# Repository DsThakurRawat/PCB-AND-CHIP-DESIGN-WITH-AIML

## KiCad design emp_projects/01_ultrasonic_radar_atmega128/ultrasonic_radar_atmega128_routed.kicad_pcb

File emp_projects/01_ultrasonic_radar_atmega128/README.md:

# Ultrasonic Radar Model Using ATmega128

## 📌 Project Overview
**Course Experiment:** Electronic Measurement Practices (EMP)  
**PCB Architecture:** 2-Layer Controlled Design  
**Primary Controller:** ATmega128A  
**Deliverables Status:** Complete Manufacturing Package Verified (Gerbers, Drill, Pos CSV, iBOM, 3D Render)

---

## 🎯 Description & Operational Principles
Panoramic ultrasonic radar mapping station with ATmega128 MCU, SG90 servo sweep platform, HC-SR04 sonar module, 16x2 HD44780 LCD readout, and RS232 host telemetry.

### Key Features & Subsystems
- **Processor & Logic Core:** High-efficiency architecture designed for reliable embedded operation.
- **Power Management & Regulation:** Low-noise power rail distribution with dedicated filtering and bulk decouple stages.
- **Sensory & Peripheral Interfacing:** Industrial standard interconnect headers with ESD and reverse polarity protection.
- **Fabrication & Assembly Optimization:** Standard 0805 SMD passives and leaded THT power devices for high manufacturing yield and inspectability.

---

## 🛠️ Bill of Materials (BOM Summary)

| Reference | Component Value | Package / Footprint | Description |
|:---:|:---:|:---:|:---|
| `U1` | **ATmega128A** | `Package_QFP:TQFP-64_14x14mm_P0.8mm` | Circuit element |
| `U2` | **MAX232** | `Package_SO:SOIC-16_3.9x9.9mm_P1.27mm` | Circuit element |
| `U3` | **LM7805** | `Package_TO_SOT_SMD:TO-252-2` | Circuit element |
| `J1` | **HC_SR04_HDR** | `Connector_PinHeader_2.54mm:PinHeader_1x04_P2.54mm_Vertical` | Circuit element |
| `J2` | **SERVO_SG90** | `Connector_PinHeader_2.54mm:PinHeader_1x03_P2.54mm_Vertical` | Circuit element |
| `J3` | **LCD_16x2_HDR** | `Connector_PinHeader_2.54mm:PinHeader_1x16_P2.54mm_Vertical` | Circuit element |
| `J4` | **AVR_ISP_6PIN** | `Connector_PinHeader_2.54mm:PinHeader_2x03_P2.54mm_Vertical` | Circuit element |
| `J5` | **PWR_JACK** | `Connector_BarrelJack:BarrelJack_Horizontal` | Circuit element |
| `Y1` | **16MHz_XTAL** | `Crystal:Crystal_SMD_3225-4Pin_3.2x2.5mm` | Circuit element |
| `C1` | **100uF_16V** | `Capacitor_THT:CP_Radial_D6.3mm_P2.50mm` | Circuit element |
| `C2` | **100nF** | `Capacitor_SMD:C_0805_2012Metric` | Circuit element |
| `R1` | **10k_RST** | `Resistor_SMD:R_0805_2012Metric` | Circuit element |
| `SW1` | **RESET** | `Button_Switch_SMD:SW_Push_SPST_NO_Alps_SKRK` | Circuit element |
| `D1` | **PWR_LED** | `LED_SMD:LED_0805_2012Metric` | Circuit element |

---

## 🏭 Manufacturing Deliverables & Artifacts

All production files have been generated in `manufacturing/`:
- **Gerber Layers (RS-274X):** Copper, solder masks, silkscreen, and board edge cuts (`manufacturing/gerbers/`)
- **Excellon Drill Files:** Plated and non-plated drill hole coordinates (`manufacturing/gerbers/*.drl`)
- **Fabricator ZIP Archive:** Single upload archive for PCB fabrication houses (`manufacturing/ultrasonic_radar_atmega128_gerbers.zip`)
- **Pick-and-Place Position CSV:** Centroid data for automated SMT placement machines (`manufacturing/ultrasonic_radar_atmega128_pos.csv`)
- **Interactive HTML BOM:** High-efficiency browser inspection and interactive assembly tool (`manufacturing/ibom.html`)
- **Altium-Style 3D Render:** Photorealistic perspective view with floor reflection shaders (`manufacturing/ultrasonic_radar_atmega128_3d.png`)

---

## 📐 Mechanical & Layout Constraints
- **Board Outline:** 100.0 mm × 75.0 mm
- **Layer Count:** 2 Layers (FR-4, 1.6mm thickness, 1oz/2oz copper)
- **Minimum Trace Width:** 0.20 mm (8 mil)
- **Minimum Clearance:** 0.20 mm (8 mil)
- **Via Drill / Diameter:** 0.40 mm drill / 0.80 mm annular ring pad

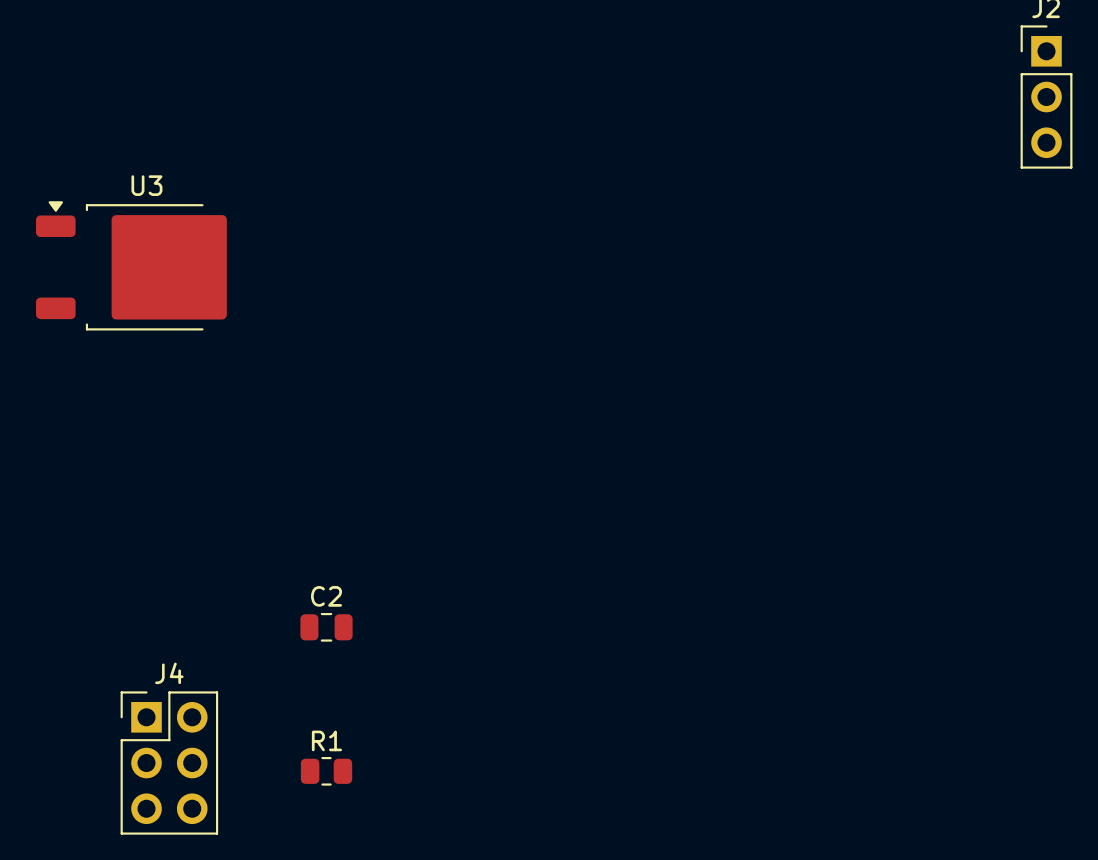
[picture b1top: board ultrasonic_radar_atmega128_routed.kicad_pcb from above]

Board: 2 copper layers, 6 parts (0 on the bottom side), 3 nets, no tracks yet.

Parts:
C2: 100nF; C_0805_2012Metric
J2: SERVO_SG90; PinHeader_1x03_P2.54mm_Vertical
J4: AVR_ISP_6PIN; PinHeader_2x03_P2.54mm_Vertical
MH3: MountingHole_M3; MountingHole_3.2mm_M3
R1: 10k_RST; R_0805_2012Metric
U3: LM7805; TO-252-2

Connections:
/+5V: C2.1, J2.1, J4.2, R1.1, U3.3
/GND: C2.2, J2.3, J4.6, U3.2
/RESET: J4.5, R1.2

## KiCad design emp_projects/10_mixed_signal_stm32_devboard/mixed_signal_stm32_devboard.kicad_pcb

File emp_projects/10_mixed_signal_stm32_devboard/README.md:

# Mixed-Signal Precision STM32 Development Board

## 📌 Project Overview
**Course Experiment:** Electronic Measurement Practices (EMP)  
**PCB Architecture:** 4-Layer Controlled Design  
**Primary Controller:** Embedded Controller  
**Deliverables Status:** Complete Manufacturing Package Verified (Gerbers, Drill, Pos CSV, iBOM, 3D Render)

---

## 🎯 Description & Operational Principles
High-precision mixed-signal laboratory development platform featuring STM32 MCU, Texas Instruments ADS1256 24-bit delta-sigma ADC, DAC8562 16-bit DAC, BNC analog I/O, and split AGND/DGND plane.

### Key Features & Subsystems
- **Processor & Logic Core:** High-efficiency architecture designed for reliable embedded operation.
- **Power Management & Regulation:** Low-noise power rail distribution with dedicated filtering and bulk decouple stages.
- **Sensory & Peripheral Interfacing:** Industrial standard interconnect headers with ESD and reverse polarity protection.
- **Fabrication & Assembly Optimization:** Standard 0805 SMD passives and leaded THT power devices for high manufacturing yield and inspectability.

---

## 🛠️ Bill of Materials (BOM Summary)

| Reference | Component Value | Package / Footprint | Description |
|:---:|:---:|:---:|:---|

---

## 🏭 Manufacturing Deliverables & Artifacts

All production files have been generated in `manufacturing/`:
- **Gerber Layers (RS-274X):** Copper, solder masks, silkscreen, and board edge cuts (`manufacturing/gerbers/`)
- **Excellon Drill Files:** Plated and non-plated drill hole coordinates (`manufacturing/gerbers/*.drl`)
- **Fabricator ZIP Archive:** Single upload archive for PCB fabrication houses (`manufacturing/mixed_signal_stm32_devboard_gerbers.zip`)
- **Pick-and-Place Position CSV:** Centroid data for automated SMT placement machines (`manufacturing/mixed_signal_stm32_devboard_pos.csv`)
- **Interactive HTML BOM:** High-efficiency browser inspection and interactive assembly tool (`manufacturing/ibom.html`)
- **Altium-Style 3D Render:** Photorealistic perspective view with floor reflection shaders (`manufacturing/mixed_signal_stm32_devboard_3d.png`)

---

## 📐 Mechanical & Layout Constraints
- **Board Outline:** 80 mm × 60 mm
- **Layer Count:** 4 Layers (FR-4, 1.6mm thickness, 1oz/2oz copper)
- **Minimum Trace Width:** 0.20 mm (8 mil)
- **Minimum Clearance:** 0.20 mm (8 mil)
- **Via Drill / Diameter:** 0.40 mm drill / 0.80 mm annular ring pad

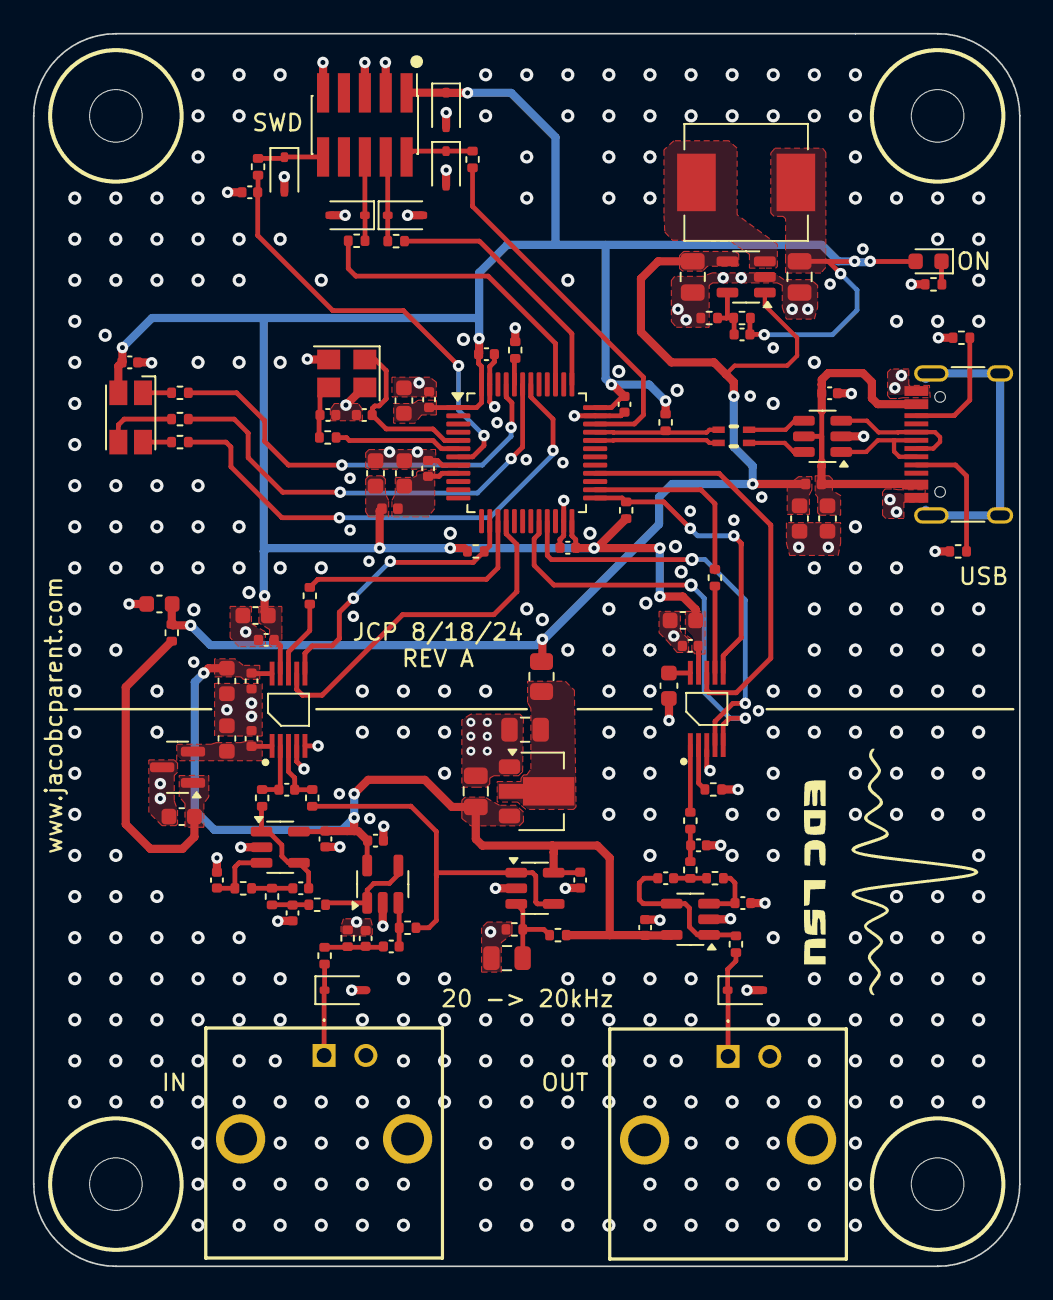
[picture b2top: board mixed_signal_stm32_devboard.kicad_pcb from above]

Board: 4 copper layers, 60.0 x 75.0 mm, 114 parts (0 on the bottom side), 68 nets.

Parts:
C100, C101, C206, C207, C402: 1u; C_0603_1608Metric
C102, C103, C104, C105, C107: 22u; C_0805_2012Metric
C106: DNP; C_0402_1005Metric
C108, C201, C202, C203, C204, C210, C211, C212, C301, C302, C306, C311, C313, C314, C401, C406: 100n; C_0402_1005Metric
C200, C308, C309, C310, C312, C315, C400: 10u; C_0603_1608Metric
C205: 10n; C_0402_1005Metric
C208, C209: 10p; C_0402_1005Metric
C300, C304, C307, C404: 150p; C_0402_1005Metric
C303, C305, C403, C405: 1n; C_0402_1005Metric
D100: GREEN; LED_0603_1608Metric
D200: ASMB-MTB1-0A3A2; LED_Avago_PLCC4_3.2x2.8mm_CW
D201, D202, D203, D204, D205, D300, D400: PESD3V3L1BA,115; D_SOD-323
H1, H2, H3, H4: MountingHole; MountingHole_3.2mm_M3
J200: USB_C_Receptacle_USB2.0; USB_C_Receptacle_HRO_TYPE-C-31-M-12
J201: 2x5 1.27mm; PinHeader_2x05_P1.27mm_Vertical_SMD
J300, J400: 031-5640-1010; BNC
L100, L200: 10n; L_0402_1005Metric
L101: 15u; L_Sunlord_MWSA0603S
L201: CMF3216F-900-2P-T; choke
R100: 10R; R_0805_2012Metric
R101: 100k; R_0402_1005Metric
R102, R304, R403: 22k; R_0402_1005Metric
R103, R104, R105, R207, R208, R209, R300, R306, R307: 1k; R_0402_1005Metric
R200, R202, R203, R401: 10k; R_0402_1005Metric
R201, R309, R400: 0R; R_0402_1005Metric
R204: 1k5; R_0402_1005Metric
R205, R206: 5k1; R_0402_1005Metric
R210, R211, R212, R213, R308, R405: 49R9; R_0402_1005Metric
R301, R302: 2M2; R_0402_1005Metric
R303, R402: 6k8; R_0402_1005Metric
R305, R404: 12k; R_0402_1005Metric
U100: HT7533-1; SOT-89-3
U101: TLV62569DBV; SOT-23-5
U102, U300, U301, U401: MCP6001T-E/OT; SOT-23-5
U200: STM32F103CBT6; LQFP-48_7x7mm_P0.5mm
U201: USBLC6-2SC6; SOT-23-6
U302: REF3033AIDBZT; SOT-23
U303: ADC141S626CIMM_NOPB; SOIC-10
U400: DAC7563SDGSR; SOIC-10
Y200: 16MHz; Crystal_SMD_3225-4Pin_3.2x2.5mm

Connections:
+3.3VA: C103.1, C108.1, C302.1, C306.1, C312.1, C313.1, C406.1, R104.2, U100.3 (VOUT), U102.5 (V+), U300.5 (V+), U301.5 (V+), U303.10 (VA), U401.5 (V+)
+3V3: C105.1, C106.1, C200.1, C201.1, C202.1, C203.1, C204.1, C207.1, C211.1, C314.1, C315.1, C400.1, C401.1, D100.2 (A), D200.4 (A), D201.1 (A1), J201.1, L101.2, L200.2, R101.2, R202.1, R203.1, R204.1, U200.1 (VBAT), U200.24 (VDD), U200.36 (VDD), U200.48 (VDD), U303.9 (VIO), U400.9 (AVDD)
+5V: C101.1, C104.1, C308.1, L100.2, R100.2, R308.2, U101.1 (EN), U101.4 (VIN)
/ADC/ADC_IN+: C307.1, R306.1, U303.2 (+IN)
/ADC/ADC_IN-: C307.2, R307.1, U303.3 (-IN)
/ADC/ADC_SCLK: R309.2, U303.8 (SCLK)
/ADC/ADC_VREF: C310.1, C311.1, U302.2 (OUT), U303.1 (VREF)
/ADC/ADC_VREF_VIN: C309.1, R308.1, U302.1 (IN)
/ADC/IN: D300.1 (A1), J300.1 (In), R300.2
/ADC/IN_AA_BUF_IN: C304.1, R305.1, U301.3 (+)
/ADC/IN_AA_BUF_OUT: C305.2, R306.2, U301.1, U301.4 (-)
/ADC/IN_BUF: C301.1, R302.1, U300.3 (+)
/ADC/IN_BUF_OUT: R303.2, U300.1, U300.4 (-)
/ADC/IN_RF: C300.1, C301.2, R300.1, R301.2
/DAC/DAC_OUT_A: R402.2, U400.1 (VOUT_A)
/DAC/DAC_OUT_B: R401.1, U400.2 (VOUT_B)
/DAC/DAC_SCLK: R400.2, U400.7 (SCLK)
/DAC/DAC_VREF: C402.1, U400.10 (VREFIN/VREFOUT)
/DAC/OUT: D400.1 (A1), J400.1 (In), R405.1
/DAC/OUT_AA_BUF_IN: C404.1, R404.1, U401.3 (+)
/DAC/OUT_AA_BUF_OUT: C405.2, R405.2, U401.1, U401.4 (-)
/MCU/BOOT0: R200.1, U200.44 (BOOT0)
/MCU/CONN_NRST: D205.1 (A1), J201.10, R213.2
/MCU/CONN_SWCLK: D203.1 (A1), J201.4, R211.2
/MCU/CONN_SWDIO: D202.1 (A1), J201.2, R210.2
/MCU/CONN_SWO: D204.1 (A1), J201.6, R212.2
/MCU/HSE_IN: C208.1, U200.5 (PD0), Y200.1
/MCU/HSE_OUT: R201.1, U200.6 (PD1)
/MCU/LED_B_K: D200.3 (BK), R209.2
/MCU/LED_G_K: D200.2 (GK), R208.2
/MCU/LED_R_K: D200.1 (RK), R207.2
/MCU/NRST: C212.1, R213.1, U200.7 (NRST)
/MCU/SWCLK: R211.1, U200.37 (PA14)
/MCU/SWDIO: R210.1, U200.34 (PA13)
/MCU/SWO: R212.1, U200.39 (PB3)
/MCU/TIM4_CH1: R208.1, U200.42 (PB6)
/MCU/TIM4_CH2: R209.1, U200.43 (PB7)
/MCU/TIM4_CH3: R207.1, U200.45 (PB8)
/MCU/USB_CMC_D+: L201.2, U201.4 (I/O2)
/MCU/USB_CMC_D-: L201.1, U201.6 (I/O1)
/MCU/USB_CONN_CC1: J200.A5 (CC1), R205.1
/MCU/USB_CONN_CC2: J200.B5 (CC2), R206.1
/MCU/USB_CONN_D+: J200.A6 (D+), J200.B6 (D+), U201.3 (I/O2)
/MCU/USB_CONN_D-: J200.A7 (D-), J200.B7 (D-), U201.1 (I/O1)
/MCU/USB_D+: L201.3, R204.2, U200.33 (PA12)
/MCU/USB_D-: L201.4, U200.32 (PA11)
/MCU/XTAL_IN: C209.1, R201.2, Y200.3
/Power/+5V_FILT: C102.1, R100.1, U100.2 (VIN)
/Power/BUCK_FB: C106.2, R101.1, R102.2, U101.5 (FB)
/Power/BUCK_SW: L101.1, U101.3 (SW)
/Power/LED_PWR_K: D100.1 (K), R103.2
/Power/VREF: C107.1, R104.1, R105.2, U102.3 (+)
DAC_NCLR: U200.20 (PB2), U400.5 (NCLR)
DAC_NLDAC: U200.21 (PB10), U400.4 (NLDAC)
GND: C100.2, C101.2, C102.2, C103.2, C104.2, C105.2, C107.2, C108.2, C200.2, C201.2, C202.2, C203.2, C204.2, C205.2, C206.2, C207.2, C208.2, C209.2, C210.2, C211.2, C212.2, C300.2, C302.2, C303.2, C304.2, C306.2, C308.2, C309.2, C310.2, C311.2, C312.2, C313.2, C314.2, C315.2, C400.2, C401.2, C402.2, C403.2, C404.2, C406.2, D201.2 (A2), D202.2 (A2), D203.2 (A2), D204.2 (A2), D205.2 (A2), D300.2 (A2), D400.2 (A2), J200.A1 (GND), J200.A12 (GND), J200.B1 (GND), J200.B12 (GND), J201.3, J201.5, J201.9, J300.2 (Ext), J300.3, J300.4, J400.2 (Ext), J400.3, J400.4, R102.1, R103.1, R105.1, R200.2, R205.2, R206.2, R301.1, R401.2, U100.1 (GND), U101.2 (GND), U102.2 (V-), U200.8 (VSSA), U200.23 (VSS), U200.35 (VSS), U200.47 (VSS), U201.2 (GND), U300.2 (V-), U301.2 (V-), U302.3 (GND), U303.4 (GND), U303.5 (GND), U400.3 (GND), U401.2 (V-), Y200.2, Y200.4
unnamed: C303.1, R303.1, R304.2
unnamed: C305.1, R304.1, R305.2
unnamed: C403.1, R402.1, R403.2
unnamed: C405.1, R403.1, R404.2
SPI1_MISO: U200.16 (PA6), U303.7 (DOUT)
SPI1_NSS: R203.2, U200.14 (PA4), U303.6 (NCS)
SPI1_SCK: R309.1, U200.15 (PA5)
SPI2_MOSI: U200.28 (PB15), U400.8 (DIN)
SPI2_NSS: R202.2, U200.25 (PB12), U400.6 (NSYNC)
SPI2_SCK: R400.1, U200.26 (PB13)
VBUS: C100.1, C210.1, J200.A4 (VBUS), J200.A9 (VBUS), J200.B4 (VBUS), J200.B9 (VBUS), L100.1, U201.5 (VBUS)
VCOM: R302.2, R307.2, U102.1, U102.4 (-)
VDDA: C205.1, C206.1, L200.1, U200.9 (VDDA)
